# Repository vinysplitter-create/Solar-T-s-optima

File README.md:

# Solar-T-s-optima

# Collaborators
1. Masika Stephanie - Supervisor

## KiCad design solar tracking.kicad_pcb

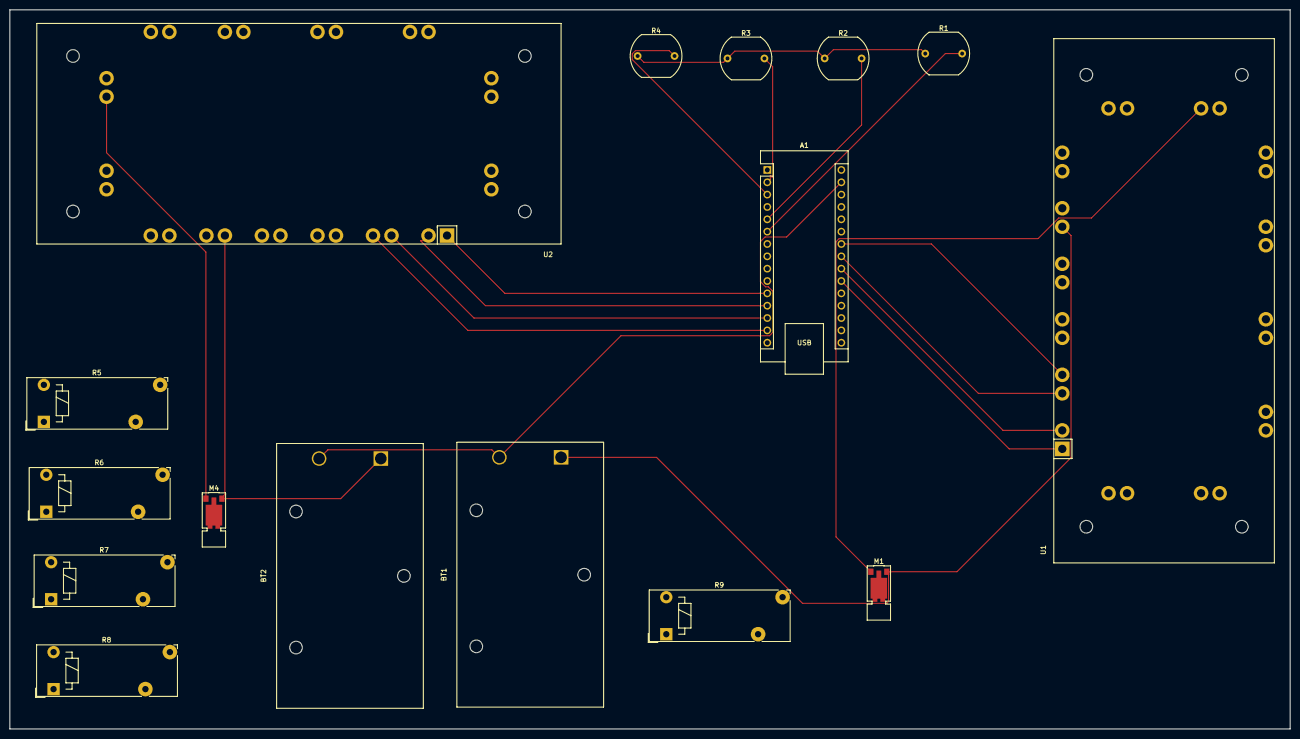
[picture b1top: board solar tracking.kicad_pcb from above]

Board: 2 copper layers, 263.5 x 148.0 mm, 16 parts (0 on the bottom side), 18 nets.

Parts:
A1: Arduino_Nano_v2.x; Arduino_Nano
BT1, BT2: Battery; BatteryHolder_Eagle_12BH611-GR
M1, M4: Stepper_Motor_unipolar_6pin; Vybronics_VZ30C1T8219732L
R1, R2, R3, R4: LDR03; R_LDR_10x8.5mm_P7.6mm_Vertical
R5, R6, R7, R8, R9: R; Relay_1-Form-A_Schrack-RYII_RM5mm
U1, U2: ULN2003A; Infineon_AG-ECONO2

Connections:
+5V: R1.1, R2.1, R3.1, R4.1
GND: A1.29 (GND), BT1.2 (-), BT2.2 (-)
unnamed: A1.21 (A2), U1.1 (I1)
unnamed: A1.22 (A3), U1.2 (I2)
unnamed: A1.23 (A4), U1.3 (I3)
unnamed: A1.24 (A5), U1.4 (I4)
unnamed: A1.2 (D0/RX), R3.2
unnamed: A1.5 (D2), R2.2
unnamed: A1.6 (D3), R1.2
unnamed: A1.11 (D8), U2.1 (I1)
unnamed: A1.12 (D9), U2.2 (I2)
unnamed: A1.13 (D10), U2.3 (I3)
unnamed: A1.14 (D11), U2.4 (I4)
unnamed: A1.3 (~RESET), R4.2
unnamed: BT1.1 (+), M1.2, U1.9 (COM)
unnamed: BT2.1 (+), M4.2, U2.9 (COM)
unnamed: M1.1, U1.15 (O2)
unnamed: M4.1, U2.15 (O2)
